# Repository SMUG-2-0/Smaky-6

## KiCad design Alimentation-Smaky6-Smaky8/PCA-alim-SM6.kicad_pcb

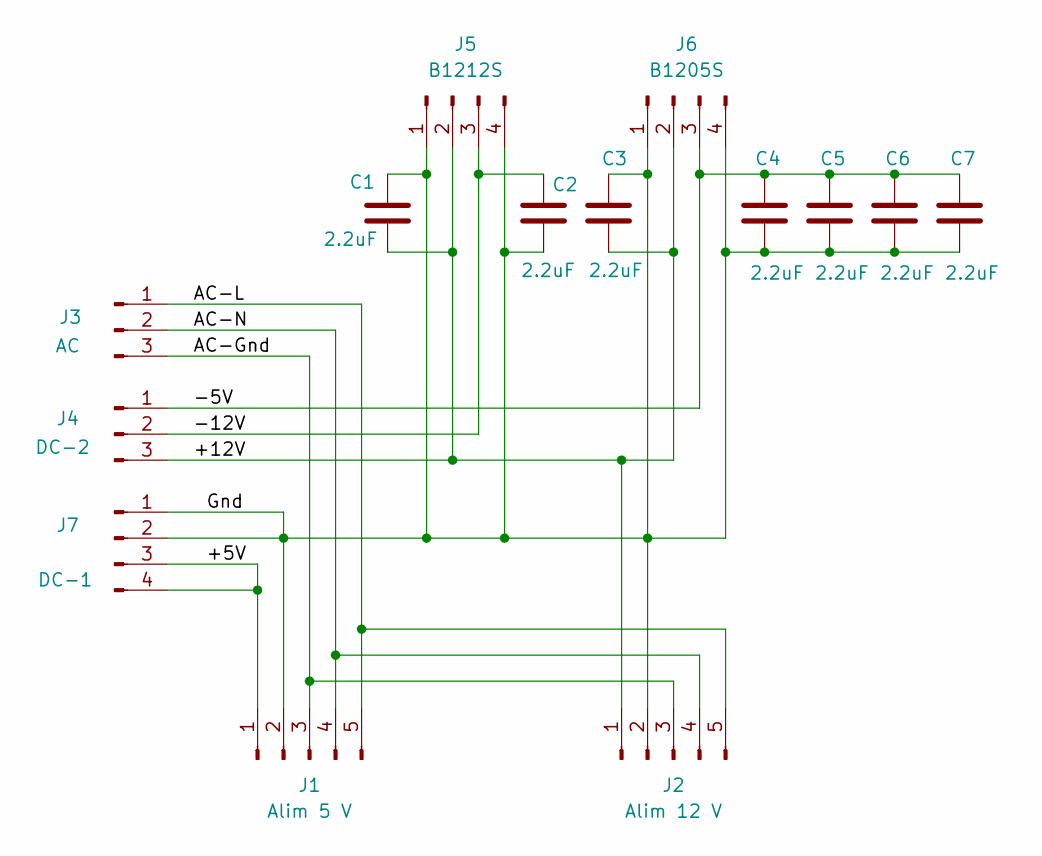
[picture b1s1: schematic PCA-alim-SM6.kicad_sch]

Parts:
C1, C2, C3, C4, C5, C6, C7: 2.2uF; C_0805_2012Metric_Pad1.18x1.45mm_HandSolder
J1: Alim 5 V; SolderWire-2.5sqmm_1x05_P8.8mm_D2.4mm_OD4.4mm
J2: Alim 12 V; SolderWire-2.5sqmm_1x05_P8.8mm_D2.4mm_OD4.4mm
J3: AC; PhoenixContact_GMSTBVA_2,5_3-G_1x03_P7.50mm_Vertical
J4: DC-2; PhoenixContact_GMSTBVA_2,5_3-G_1x03_P7.50mm_Vertical
J5: B1212S; PinHeader_1x04_P2.54mm_Vertical
J6: B1205S; PinHeader_1x04_P2.54mm_Vertical
J7: DC-1; PhoenixContact_GMSTBVA_2,5_4-G_1x04_P7.50mm_Vertical

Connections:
/+5V: J1.1, J7.3, J7.4
/+12V: C1.2, C3.2, J2.1, J4.3, J5.2, J6.2
/-5V: C4.1, C5.1, C6.1, C7.1, J4.1, J6.3
/-12V: C2.1, J4.2, J5.3
/AC-Gnd: J1.3, J2.3, J3.3
/AC-L: J1.5, J2.5, J3.1
/AC-N: J1.4, J2.4, J3.2
/Gnd: C1.1, C2.2, C3.1, C4.2, C5.2, C6.2, C7.2, J1.2, J2.2, J5.1, J5.4, J6.1, J6.4, J7.1, J7.2

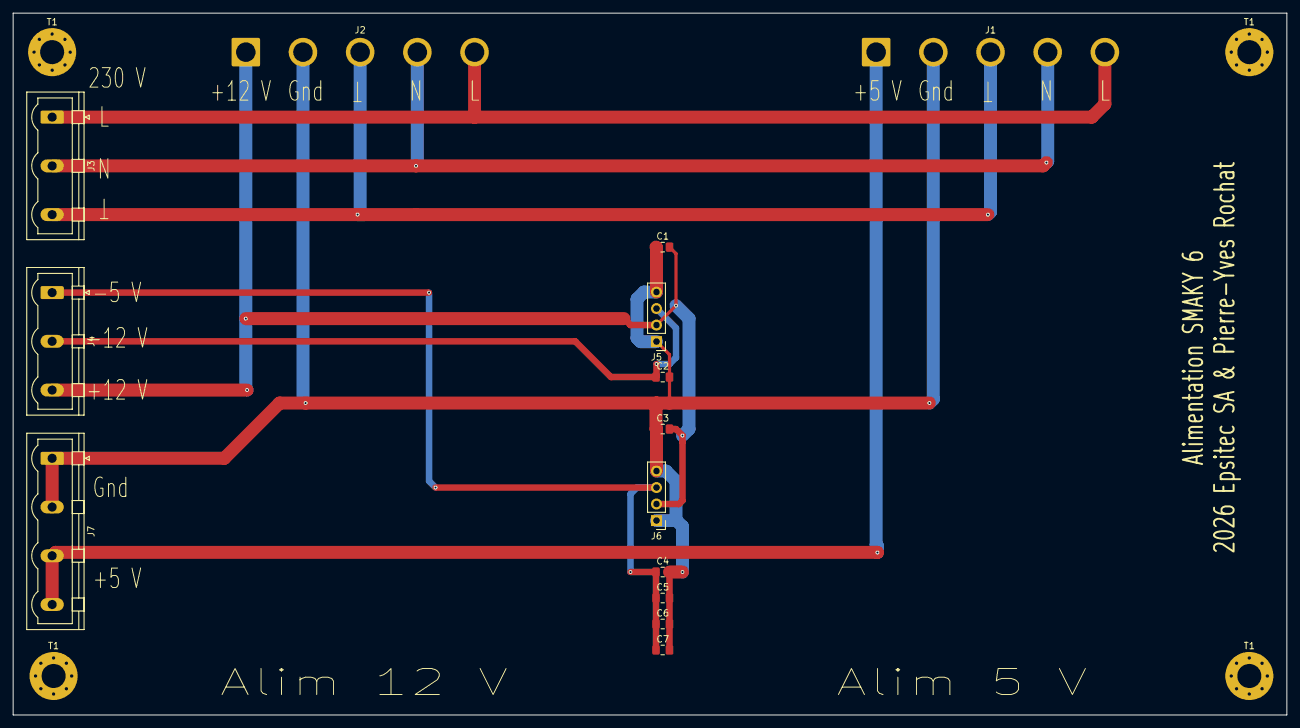
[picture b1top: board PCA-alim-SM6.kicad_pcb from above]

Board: 2 copper layers, 196.0 x 108.0 mm, 18 parts (0 on the bottom side), 8 nets.

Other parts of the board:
T1, T1#2, T1#3, T1#4: MountingHole_3.7mm_Pad_Via

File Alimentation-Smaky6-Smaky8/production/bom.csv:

Designator,Footprint,Quantity,Value,LCSC Part #
"C1, C2, C3, C4, C5, C6, C7",0805,7,2.2uF,
J1,SolderWire-2.5sqmm_1x05_P8.8mm_D2.4mm_OD4.4mm,1,Alim 5 V,
J2,SolderWire-2.5sqmm_1x05_P8.8mm_D2.4mm_OD4.4mm,1,Alim 12 V,
J3,"PhoenixContact_GMSTBVA_2,5_3-G_1x03_P7.50mm_Vertical",1,AC,
J4,"PhoenixContact_GMSTBVA_2,5_3-G_1x03_P7.50mm_Vertical",1,DC-2,
J5,PinHeader_1x04_P2.54mm_Vertical,1,B1212S,
J6,PinHeader_1x04_P2.54mm_Vertical,1,B1205S,
J7,"PhoenixContact_GMSTBVA_2,5_4-G_1x04_P7.50mm_Vertical",1,DC-1,

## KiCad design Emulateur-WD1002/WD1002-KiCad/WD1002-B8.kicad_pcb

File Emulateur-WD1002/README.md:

# Emulateur de contrôleur de disque dur pour Smaky 6

Les disques durs datant du début des années 1980 sont rares à fonctionner encore actuellement.
Même les lecteurs de disquettes Micropolis des Smaky 6 fonctionnent souvent très mal après plus de 40 ans.
Par contre, les Smaky 6 eux-même fonctionnent souvent encore très bien, surtout lorsqu'on prend la peine de leur mettre des alimentations plus modernes.

Il nous a donc semblé utile de concevoir une émulateur du contrôleur original de disque dur des Smaky 6, le contrôleurs WD1000, WD1001 et WD1002. 
Ces contrôleurs sont bien documentés :

[Documentation du WD1002](http://www.bitsavers.org/pdf/westernDigital/WD100x/61-031050-0030_WD1002-05_HDO_OEM_Manual_Jul83.pdf)

Le circuit utilise un microcontrôleur **STM32**, cadençé à une fréquence suffisante (180 MHz) pour pouvoir répondre aux requêtes du Z80.
Branché sur le connecteur **MUBUS-26**, au bord droit de la carte mêre du Smaky 6, il possède un socle pour une carte micr-SD, qui contient des images de disques ou disquettes Smaky 6.

Le dossier WD1002SD contient le projet complet pour le firmware de l'émulateur.
C'est un projet STM32cubeIDE.

Le dossier WD1002-KiCAD contient le circuit imprimé sous forme d'un projet KiCad,
dont voici le schéma : [Schéma émulateur WD1002](WD1002-schema.pdf)

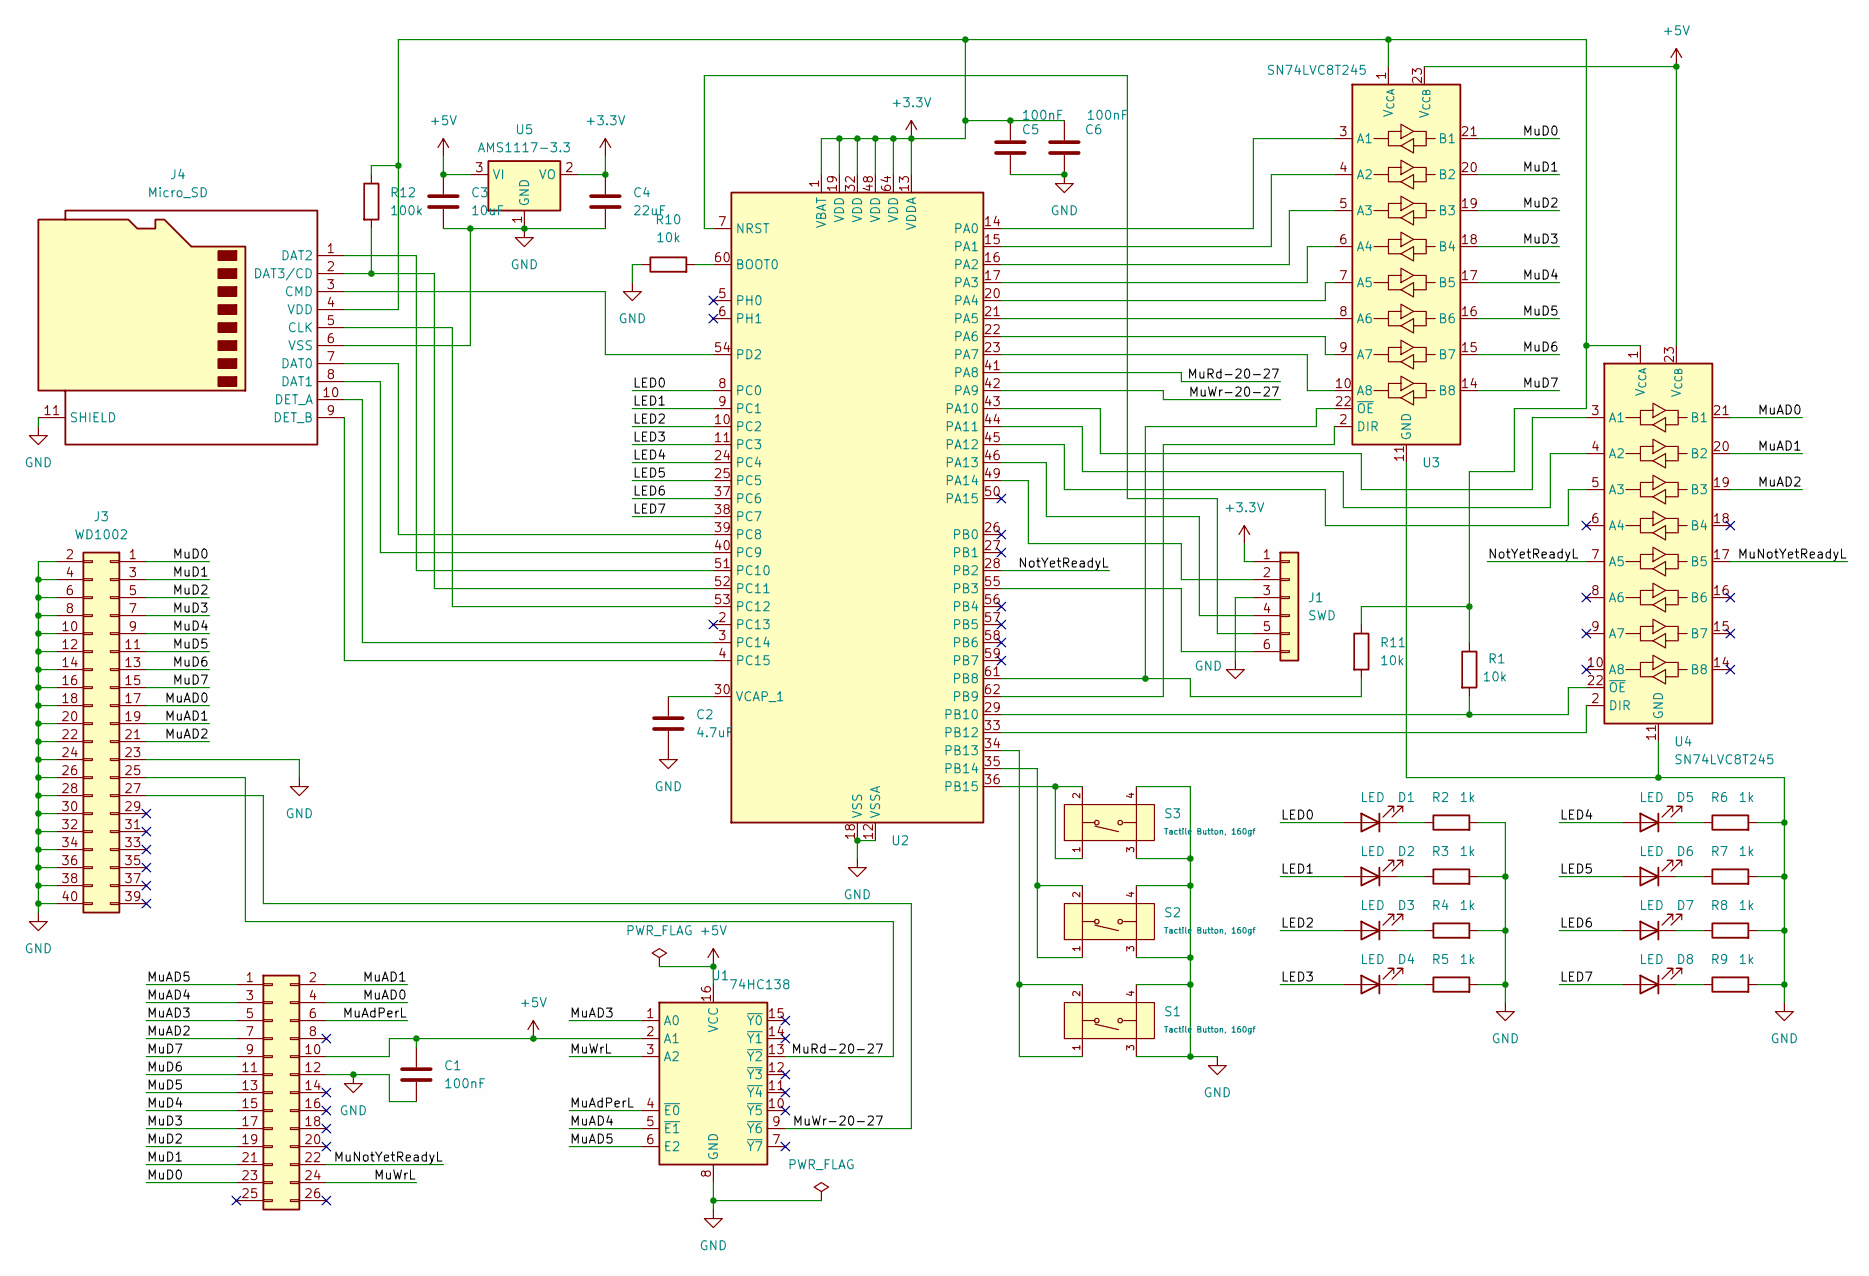
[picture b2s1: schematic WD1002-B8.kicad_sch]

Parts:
C1: 100nF; C_0603_1608Metric_Pad1.08x0.95mm_HandSolder
C2: 4.7uF; C_0603_1608Metric
C3: 10uF; C_1206_3216Metric
C4: 22uF; C_1206_3216Metric
C5, C6: 100nF; C_0603_1608Metric
D1, D2, D3, D4, D5, D6, D7, D8: LED; LED_0603_1608Metric
J1: SWD; PinHeader_1x06_P2.54mm_Horizontal
J3: WD1002; PinHeader_2x20_P2.54mm_Vertical
J4: Micro_SD; microSD_HC_Hirose_DM3AT-SF-PEJM5
Mubus26: Conn_02x13_Odd_Even; PinHeader_2x13_P2.54mm_Vertical
R1, R10, R11: 10k; R_0603_1608Metric
R2, R3, R4, R5, R6, R7, R8, R9: 1k; R_0603_1608Metric
R12: 100k; R_0603_1608Metric
S1, S2, S3: Tactile Button, 160gf; SW-SMD_4P-L5.1-W5.1-P3.70-LS6.5-TL-2; Voltage Rating (Dc) 12V; Part TS-1187A-B-A-B; LCSC C318884
U1: 74HC138; SOIC-16_3.9x9.9mm_P1.27mm
U2: STM32F446RETx; LQFP-64_10x10mm_P0.5mm
U3, U4: SN74LVC8T245; TSSOP-24_4.4x7.8mm_P0.65mm
U5: AMS1117-3.3; SOT-223-3_TabPin2

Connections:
+3.3V: C4.1, C5.1, C6.1, J1.1, J4.4 (VDD), R1.1, R11.1, R12.1, U2.1 (VBAT), U2.13 (VDDA), U2.19 (VDD), U2.32 (VDD), U2.48 (VDD), U2.64 (VDD), U3.1 (V_{CCA}), U4.1 (V_{CCA}), U5.2 (VO)
+5V: C1.1, C3.1, Mubus26.10, U1.2 (A1), U1.16 (VCC), U3.23 (V_{CCB}), U3.24 (V_{CCB}), U4.23 (V_{CCB}), U4.24 (V_{CCB}), U5.3 (VI)
/LED0: D1.2 (A), U2.8 (PC0)
/LED1: D2.2 (A), U2.9 (PC1)
/LED2: D3.2 (A), U2.10 (PC2)
/LED3: D4.2 (A), U2.11 (PC3)
/LED4: D5.2 (A), U2.24 (PC4)
/LED5: D6.2 (A), U2.25 (PC5)
/LED6: D7.2 (A), U2.37 (PC6)
/LED7: D8.2 (A), U2.38 (PC7)
/MuAD0: J3.17, Mubus26.4, U4.21 (B1)
/MuAD1: J3.19, Mubus26.2, U4.20 (B2)
/MuAD2: J3.21, Mubus26.7, U4.19 (B3)
/MuAD3: Mubus26.5, U1.1 (A0)
/MuAD4: Mubus26.3, U1.5 (~E1)
/MuAD5: Mubus26.1, U1.6 (E2)
/MuAdPerL: Mubus26.6, U1.4 (~E0)
/MuD0: J3.1, Mubus26.23, U3.21 (B1)
/MuD1: J3.3, Mubus26.21, U3.20 (B2)
/MuD2: J3.5, Mubus26.19, U3.19 (B3)
/MuD3: J3.7, Mubus26.17, U3.18 (B4)
/MuD4: J3.9, Mubus26.15, U3.17 (B5)
/MuD5: J3.11, Mubus26.13, U3.16 (B6)
/MuD6: J3.13, Mubus26.11, U3.15 (B7)
/MuD7: J3.15, Mubus26.9, U3.14 (B8)
/MuNotYetReadyL: Mubus26.22, U4.17 (B5)
/MuRd-20-27: J3.25, U1.13 (~Y2), U2.41 (PA8)
/MuWr-20-27: J3.27, U1.9 (~Y6), U2.42 (PA9)
/MuWrL: Mubus26.24, U1.3 (A2)
/NotYetReadyL: U2.28 (PB2), U4.7 (A5)
GND: C1.2, C2.2, C3.2, C4.2, C5.2, C6.2, J1.3, J3.2, J3.4, J3.6, J3.8, J3.10, J3.12, J3.14, J3.16, J3.18, J3.20, J3.22, J3.23, J3.24, J3.26, J3.28, J3.30, J3.32, J3.34, J3.36, J3.38, J3.40, J4.6 (VSS), J4.11 (SHIELD), Mubus26.12, R2.2, R3.2, R4.2, R5.2, R6.2, R7.2, R8.2, R9.2, R10.1, S1.3 (C), S1.4 (D), S2.3 (C), S2.4 (D), S3.3 (C), S3.4 (D), U1.8 (GND), U2.12 (VSSA), U2.18 (VSS), U2.31 (VSS), U2.47 (VSS), U2.63 (VSS), U3.11 (GND), U3.12 (GND), U3.13 (GND), U4.11 (GND), U4.12 (GND), U4.13 (GND), U5.1 (GND)
unnamed: D1.1 (K), R2.1
unnamed: D2.1 (K), R3.1
unnamed: D3.1 (K), R4.1
unnamed: D4.1 (K), R5.1
unnamed: D5.1 (K), R6.1
unnamed: D6.1 (K), R7.1
unnamed: D7.1 (K), R8.1
unnamed: D8.1 (K), R9.1
unnamed: J1.2, U2.49 (PA14)
unnamed: J1.4, U2.46 (PA13)
unnamed: J1.5, U2.7 (NRST)
unnamed: J1.6, U2.55 (PB3)
unnamed: J4.5 (CLK), U2.53 (PC12)
unnamed: J4.3 (CMD), U2.54 (PD2)
unnamed: J4.7 (DAT0), U2.39 (PC8)
unnamed: J4.8 (DAT1), U2.40 (PC9)
unnamed: J4.1 (DAT2), U2.51 (PC10)
unnamed: J4.2 (DAT3/CD), R12.2, U2.52 (PC11)
unnamed: J4.10 (DET_A), U2.3 (PC14)
unnamed: J4.9 (DET_B), U2.4 (PC15)
unnamed: S1.1 (A), S1.2 (B), U2.34 (PB13)
unnamed: S2.1 (A), S2.2 (B), U2.35 (PB14)
unnamed: S3.1 (A), S3.2 (B), U2.36 (PB15)
unnamed: R10.2, U2.60 (BOOT0)
unnamed: U2.14 (PA0), U3.3 (A1)
unnamed: U2.15 (PA1), U3.4 (A2)
unnamed: U2.16 (PA2), U3.5 (A3)
unnamed: U2.17 (PA3), U3.6 (A4)
unnamed: U2.20 (PA4), U3.7 (A5)
unnamed: U2.21 (PA5), U3.8 (A6)
unnamed: U2.22 (PA6), U3.9 (A7)
unnamed: U2.23 (PA7), U3.10 (A8)
unnamed: U2.43 (PA10), U4.3 (A1)
unnamed: U2.44 (PA11), U4.4 (A2)
unnamed: U2.45 (PA12), U4.5 (A3)
unnamed: R11.2, U2.61 (PB8), U3.22 (~OE)
unnamed: U2.62 (PB9), U3.2 (DIR)
unnamed: R1.2, U2.29 (PB10), U4.22 (~OE)
unnamed: U2.33 (PB12), U4.2 (DIR)
unnamed: C2.1, U2.30 (VCAP_1)

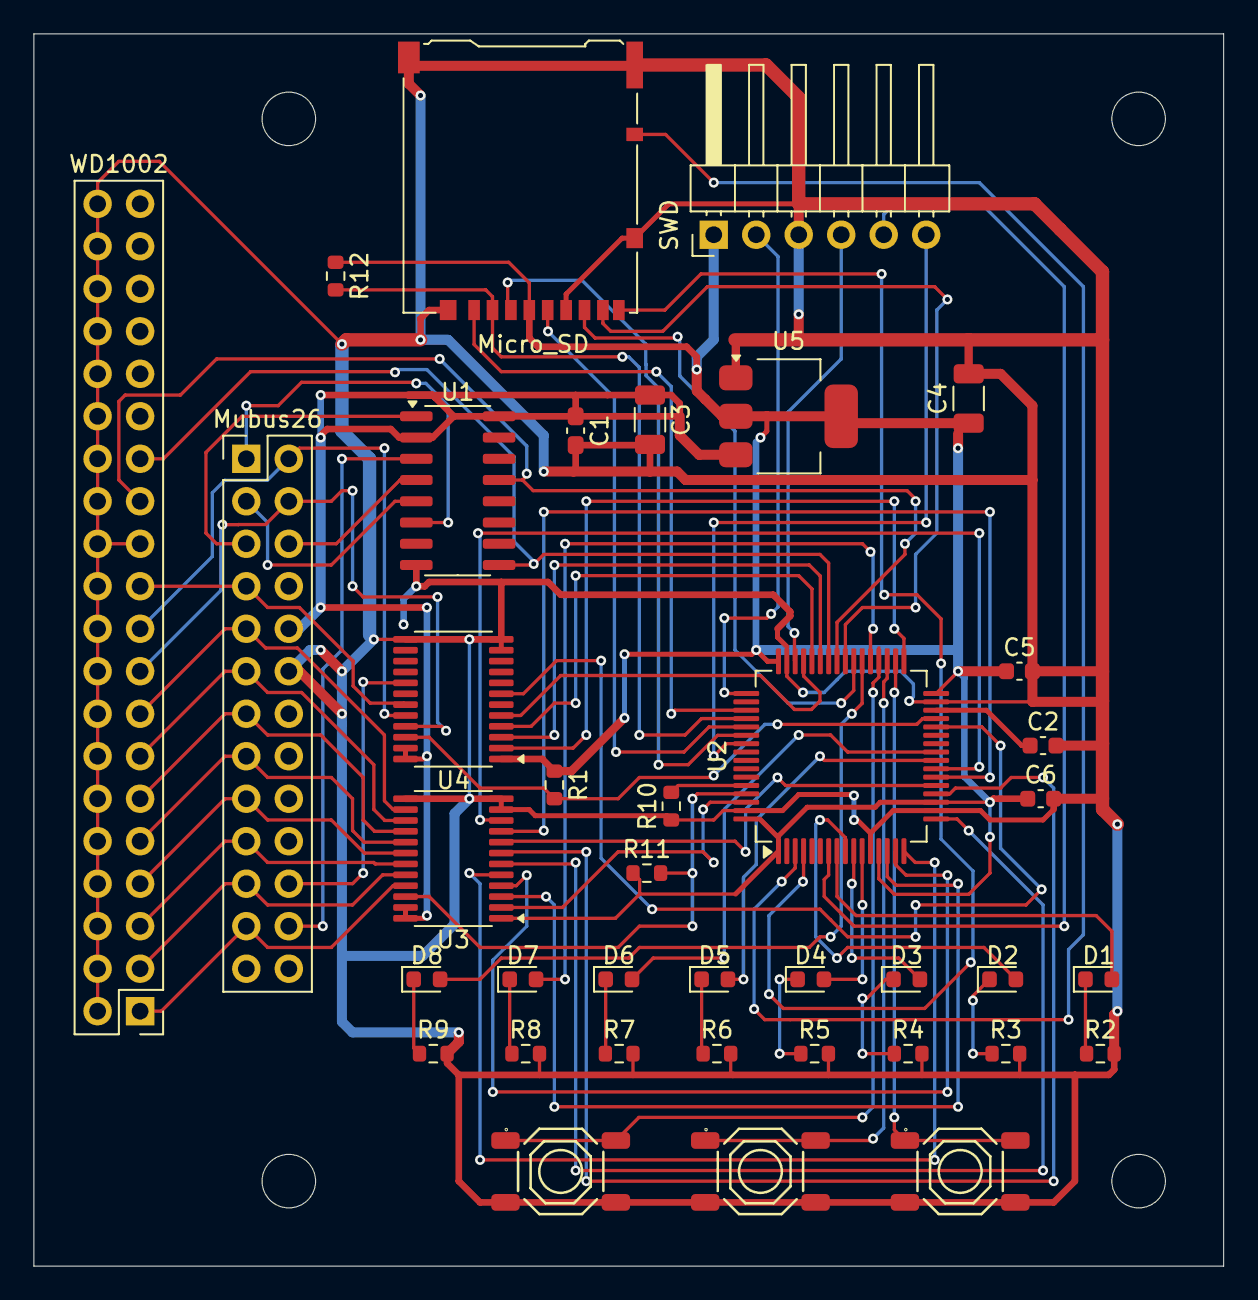
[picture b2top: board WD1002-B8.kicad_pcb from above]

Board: 2 copper layers, 71.1 x 73.7 mm, 38 parts (0 on the bottom side), 71 nets.

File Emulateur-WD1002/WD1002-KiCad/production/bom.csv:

Designator,Footprint,Quantity,Value,LCSC Part #
"C1, C5, C6",0603,3,100nF,
C2,0603,1,4.7uF,
C3,1206,1,10uF,
C4,1206,1,22uF,
"D1, D2, D3, D4, D5, D6, D7, D8",0603,8,LED,
J1,PinHeader_1x06_P2.54mm_Horizontal,1,SWD,
J3,PinHeader_2x20_P2.54mm_Vertical,1,WD1002,
J4,microSD_HC_Hirose_DM3AT-SF-PEJM5,1,Micro_SD,
MUBUS26,PinHeader_2x13_P2.54mm_Vertical,1,Conn_02x13_Odd_Even,
"R1, R10, R11",0603,3,10k,
R12,0603,1,100k,
"R2, R3, R4, R5, R6, R7, R8, R9",0603,8,1k,
"S1, S2, S3",SW-SMD_4P-L5.1-W5.1-P3.70-LS6.5-TL-2,3,"Tactile Button, 160gf",C318884
U1,SOIC-16_3.9x9.9mm_P1.27mm,1,74HC138,
U2,LQFP-64_10x10mm_P0.5mm,1,STM32F446RETx,
"U3, U4",TSSOP-24_4.4x7.8mm_P0.65mm,2,SN74LVC8T245,
U5,SOT-223-3_TabPin2,1,AMS1117-3.3,

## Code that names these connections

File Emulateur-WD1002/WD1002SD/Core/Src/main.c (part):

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/* USER CODE BEGIN PD */

// #define GPIO_NOT_YET_READY GPIOD // ancienne carte
#define GPIO_NOT_YET_READY GPIOB // carte avec microSD (PD2 utilisé par SD)

/* USER CODE END PD */

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  HAL_GPIO_WritePin(GPIO_NOT_YET_READY, GPIO_PIN_2, 0); // Prépare le NotYetReady

  GPIOB->BSRR = GPIO_BSRR_BR_9; // DIR data à 0
  // GPIO_NOT_YET_READY->MODER = 0b010000; // PD2 (PB2) en sortie, active NotYetReadyL, pas passé !

  /* USER CODE END 2 */

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  __HAL_RCC_GPIOD_CLK_ENABLE();

  /*Configure GPIO pin Output Level */
  HAL_GPIO_WritePin(GPIOC, GPIO_PIN_13|Led1_Pin|Led2_Pin|Led3_Pin
                          |Led4_Pin|Led5_Pin|Led6_Pin|Led7_Pin
                          |Led8_Pin, GPIO_PIN_RESET);

  HAL_GPIO_WritePin(GPIOB, GPIO_PIN_2|GPIO_PIN_8|GPIO_PIN_9|GPIO_PIN_10|GPIO_PIN_12
		  	  	  	  	  , GPIO_PIN_RESET);

  /*Configure GPIO pins : PC13 Led1_Pin Led2_Pin Led3_Pin
                           Led4_Pin Led5_Pin Led6_Pin Led7_Pin
                           Led8_Pin */
  GPIO_InitStruct.Pin = GPIO_PIN_15|GPIO_PIN_13|Led1_Pin|Led2_Pin|Led3_Pin
                          |Led4_Pin|Led5_Pin|Led6_Pin|Led7_Pin
                          |Led8_Pin;
  GPIO_InitStruct.Mode = GPIO_MODE_OUTPUT_PP;
  GPIO_InitStruct.Pull = GPIO_NOPULL;
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  GPIO_InitStruct.Speed = GPIO_SPEED_FREQ_VERY_HIGH; //GPIO_SPEED_FREQ_VERY_HIGH; //GPIO_SPEED_FREQ_HIGH;
  HAL_GPIO_Init(GPIOB, &GPIO_InitStruct);

  /*Configure GPIO pins : MuD0_Pin MuD1_Pin MuD2_Pin MuD3_Pin
                           MuD4_Pin MuD5_Pin MuD6_Pin MuD7_Pin
                           MuAD0_Pin MuAD1_Pin MuAD2_Pin */
  GPIO_InitStruct.Pin = MuD0_Pin|MuD1_Pin|MuD2_Pin|MuD3_Pin //*********************** Data
                          |MuD4_Pin|MuD5_Pin|MuD6_Pin|MuD7_Pin
                          |MuAD0_Pin|MuAD1_Pin|MuAD2_Pin;
  GPIO_InitStruct.Mode = GPIO_MODE_INPUT;
  GPIO_InitStruct.Speed = GPIO_SPEED_FREQ_VERY_HIGH; // pour l'autre direction
  GPIO_InitStruct.Pull = GPIO_PULLDOWN;
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  GPIO_InitStruct.Pull = GPIO_NOPULL;
  HAL_GPIO_Init(MuWr20_27_GPIO_Port, &GPIO_InitStruct);

  /*Configure GPIO pin : PD2 = NotYetReady, passé à PB2 */
  GPIO_InitStruct.Pin = GPIO_PIN_2;
  GPIO_InitStruct.Mode = GPIO_MODE_OUTPUT_PP;
  GPIO_InitStruct.Pull = GPIO_NOPULL;
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
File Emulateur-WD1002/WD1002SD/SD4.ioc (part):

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Mcu.Name=STM32F446R(C-E)Tx
Mcu.Package=LQFP64
Mcu.UserName=STM32F446RETx
PB13.GPIOParameters=GPIO_PuPd
PB13.GPIO_PuPd=GPIO_PULLUP
PB13.Signal=GPIO_Input
PB14.GPIOParameters=GPIO_PuPd
PB14.GPIO_PuPd=GPIO_PULLUP
PB14.Signal=GPIO_Input
PB15.GPIOParameters=GPIO_PuPd
PB15.GPIO_PuPd=GPIO_PULLUP
PB15.Signal=GPIO_Input
PC0.Signal=GPIO_Output
PC1.Signal=GPIO_Output
PC12.Mode=SD_1_bit
PC12.Signal=SDIO_CK
PC14-OSC32_IN.Signal=GPIO_Input
PC15-OSC32_OUT.Signal=GPIO_Output
PC2.Signal=GPIO_Output
PC3.Signal=GPIO_Output
PC4.Signal=GPIO_Output
PC5.Signal=GPIO_Output
PC6.Signal=GPIO_Output
PC7.Signal=GPIO_Output
PC8.GPIOParameters=GPIO_PuPd
PC8.GPIO_PuPd=GPIO_PULLUP
PC8.Mode=SD_1_bit
PC8.Signal=SDIO_D0
PC9.GPIOParameters=GPIO_PuPd
PC9.GPIO_PuPd=GPIO_PULLUP
PC9.Signal=SDIO_D1
PD2.GPIOParameters=GPIO_PuPd
PD2.GPIO_PuPd=GPIO_PULLUP
PD2.Mode=SD_1_bit
PD2.Signal=SDIO_CMD
board=custom

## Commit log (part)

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2026-03-02 Initial empty README
2026-03-02 Premier jet !
2026-03-06 Emulateur: fichiers KiCad et STM32, photo et schema
2026-03-06 Programmes d'extraction simplifié et complété, 3 images + dossier des fichiers
2026-03-06 Quelques corrections...
2026-05-08 Ajout du Simulateur-JS : émulation Z80 + Smaky 6 (port JS, version 0.3.0)
2026-05-08 rom18.js : suppression du BOM UTF-8 (cohérence avec le reste du projet)
2026-05-08 release.md : aide-mémoire workflow Git et liens de téléchargement
2026-05-08 Simulateur-JS : ajout d'un README.md (présentation et liens des installateurs)
2026-05-08 Copie d'écran dans le README

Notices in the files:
Emulateur-WD1002/WD1002SD/Core/Src/main.c:
Copyright (c) 2025 STMicroelectronics.
All rights reserved.
This software is licensed under terms that can be found in the LICENSE file
